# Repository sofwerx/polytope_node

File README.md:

# polytope_node
Compute/Sensor node for Polytope

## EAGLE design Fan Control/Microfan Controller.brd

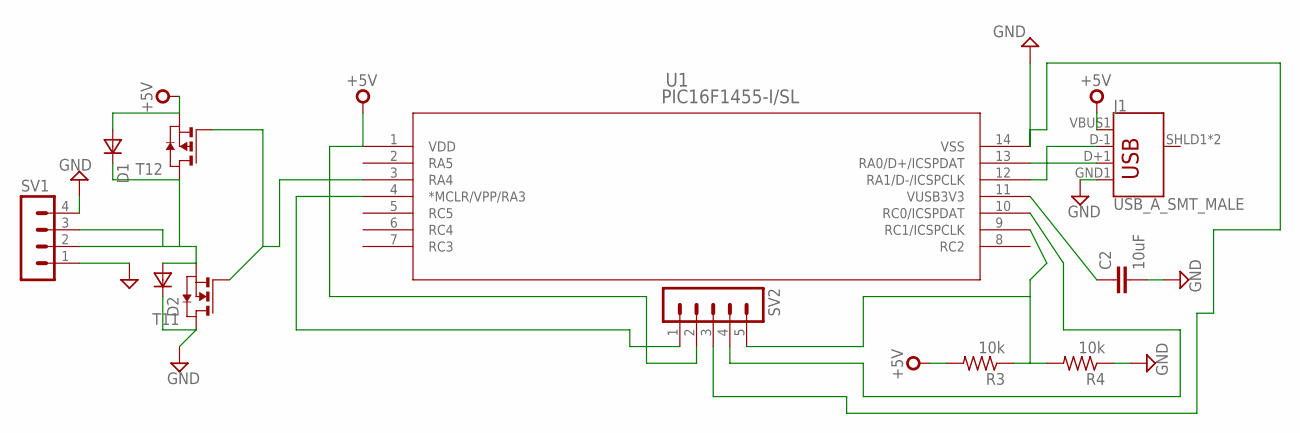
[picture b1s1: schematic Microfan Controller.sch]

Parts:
C2: 10uF; C0805
D1, D2: VAR2SOT23; SOT-23
J1: USB_A_SMT_MALE; USB-A-SMT-MALE
R3, R4: 10k; R0805
SV1: MA04-1
SV2: MA05-1
T1: PN_MOSFET-MSOP8; MSOP8
U1: PIC16F1455-I/SL; SOIC14_SL

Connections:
+5V: D1.3 (A), J1.VBUS1 (VBUS), R3.2, SV2.2, T1.3 (S), U1.1 (VDD)
GND: C2.2, D2.1 (C), J1.GND1 (GND), R4.1, SV1.1, SV1.4, T1.7 (D), T1.8 (D)
unnamed: SV2.1, U1.4 (*MCLR/VPP/RA3)
unnamed: J1.D-1 (D-), U1.12 (RA1/D-/ICSPCLK)
unnamed: T1.2 (G), T1.4 (G), U1.3 (RA4)
unnamed: R3.1, R4.2, SV2.5, U1.9 (RC1/ICSPCLK)
unnamed: D1.1 (C), D2.3 (A), SV1.2, SV1.3, T1.1 (S), T1.5 (D), T1.6 (D)
unnamed: J1.D+1 (D+), U1.13 (RA0/D+/ICSPDAT)
unnamed: SV2.3, U1.14 (VSS)
unnamed: SV2.4, U1.10 (RC0/ICSPDAT)
VUSB3V3: U1.11 (VUSB3V3)

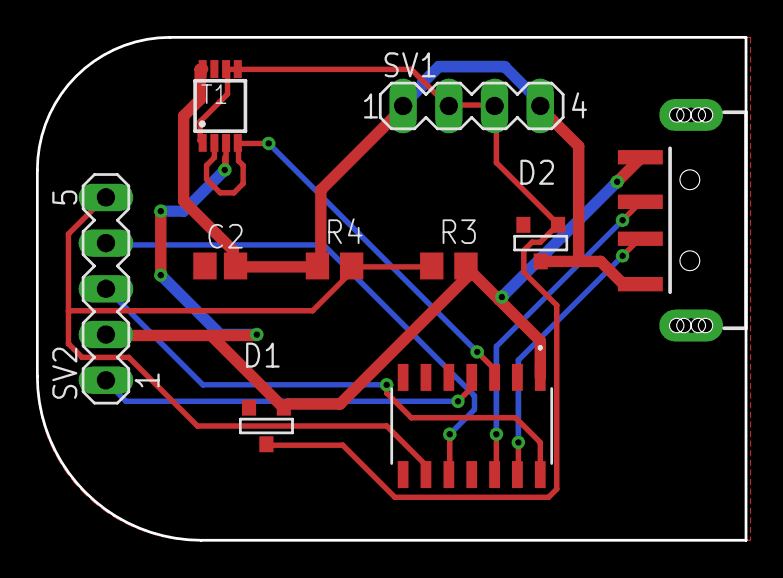
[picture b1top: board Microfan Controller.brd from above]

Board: 2 copper layers, 39.4 x 27.9 mm, 10 parts (0 on the bottom side), 10 nets.

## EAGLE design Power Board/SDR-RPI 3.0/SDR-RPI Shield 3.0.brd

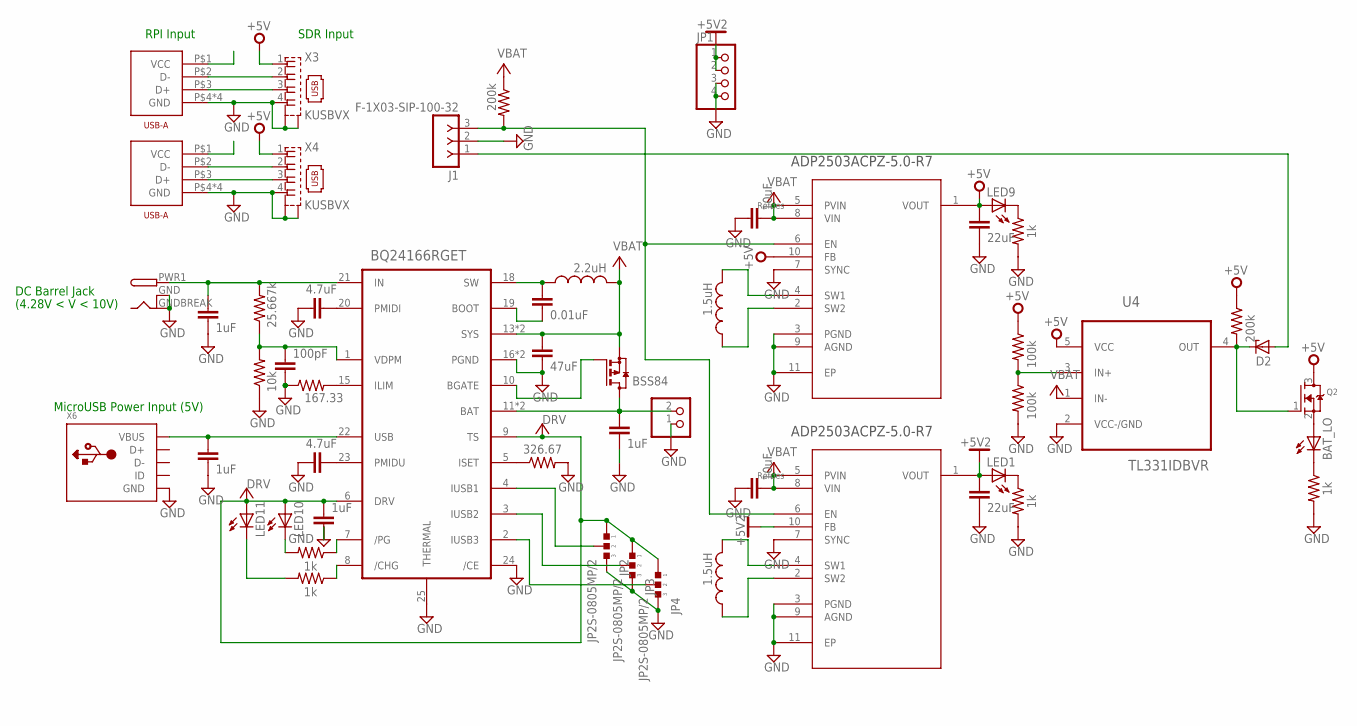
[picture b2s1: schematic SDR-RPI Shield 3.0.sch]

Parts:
BAT_LO: LED_ESML0603; LED_SML0603
C1, C3, C5, C8: 1uF; C0805
C2, C4: 4.7uF; C0805
C6: 0.01uF; C0805
C7, C12: 22uF; C0805
C9: 47uF; C0805
C10, C11: 10uF; C0805
C17: 100pF; C0805
CN1: JST_2PIN-SMT; JST-PH-2-SMT
CN3: DCBARRELSMT; DCJACK_2MM_SMT
D2: ZENER-DIODESOD80C; SOD80C
J1: F-1X03-SIP-100-32; SIP-100-03-32
JP1: PINHD-1X4; 1X04
JP2, JP3, JP4: JP2S-0805MP/2; R0805MP/2
L1: 2.2uH; L1812
L2, L3: 1.5uH; L1812
LED1, LED9, LED10, LED11: LED_ESML0603; LED_SML0603
Q1: BSS84; SOT23
Q2: MOSFET-NREFLOW; SOT23
R1: 25.667k; M0805
R2: 10k; M0805
R3: 167.33; M0805
R4, R5, R7, R8, R12: 1k; M0805
R6: 326.67; M0805
R9, R10: 100k; M0805
R11, R16: 200k; M0805
U1: BQ24166RGET; QFN50P400X400X100-25N
U2, U3: ADP2503ACPZ-5.0-R7; DFN300X300X80-11N
U4: TL331IDBVR; SOT95P280X145-5N
U$1, U$2: USB-A
X3, X4: KUSBVX
X6: USB_MICRO_20329_V2; 4UCONN_20329_V2

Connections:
+5V: C12.1, LED9.A, Q2.3 (D), R9.1, R11.1, U3.1 (VOUT), U3.10 (FB), U4.5 (VCC), X3.1, X4.1
+5V2: C7.1, JP1.1, JP1.2, LED1.A, U2.1 (VOUT), U2.10 (FB)
DRV: C5.1, JP2.1, JP3.1, JP4.1, LED10.A, LED11.A, U1.6 (DRV), U1.9 (TS)
GND: C1.2, C2.2, C3.2, C4.2, C5.2, C7.2, C8.2, C9.2, C10.1, C11.1, C12.2, C17.2, CN1.1 (2), CN3.GND (GNDBREAK), CN3.GNDBREAK (GND), J1.2, JP1.3, JP1.4, JP2.3, JP3.3, JP4.3, R2.1, R3.1, R6.2, R7.2, R8.2, R10.2, R12.2, U1.16 (PGND), U1.17 (PGND), U1.24 (/CE), U1.25 (THERMAL), U2.3 (PGND), U2.7 (SYNC), U2.9 (AGND), U2.11 (EP), U3.3 (PGND), U3.7 (SYNC), U3.9 (AGND), U3.11 (EP), U4.2 (VCC-/GND), U$1.P$4 (GND), U$1.P$5 (GND), U$1.P$6 (GND), U$1.P$8 (GND), U$2.P$4 (GND), U$2.P$5 (GND), U$2.P$6 (GND), U$2.P$8 (GND), X3.4, X3.M1 (S1), X3.M2 (S2), X4.4, X4.M1 (S1), X4.M2 (S2), X6.BASE@1 (GND), X6.BASE@2 (GND), X6.GND, X6.SPRT@1 (GND), X6.SPRT@2 (GND), X6.SPRT@3 (GND), X6.SPRT@4 (GND)
unnamed: C17.1, R1.1, R2.2, U1.1 (VDPM)
unnamed: R4.1, U1.7 (/PG)
unnamed: R5.1, U1.8 (/CHG)
unnamed: C1.1, CN3.PWR1 (PWR), R1.2, U1.21 (IN)
unnamed: C2.1, U1.20 (PMIDI)
unnamed: R3.2, U1.15 (ILIM)
unnamed: C3.1, U1.22 (USB), X6.VBUS
unnamed: C4.1, U1.23 (PMIDU)
unnamed: Q1.1 (G), U1.10 (BGATE)
unnamed: LED10.C, R4.2
unnamed: C6.2, U1.19 (BOOT)
unnamed: LED11.C, R5.2
unnamed: C6.1, L1.1, U1.18 (SW)
unnamed: J1.3, R16.2, U2.6 (EN), U3.6 (EN)
unnamed: L2.2, U3.4 (SW1)
unnamed: L2.1, U3.2 (SW2)
unnamed: C8.1, CN1.2 (1), Q1.3 (D), U1.11 (BAT), U1.12 (BAT)
unnamed: R6.1, U1.5 (ISET)
unnamed: R9.2, R10.1, U4.3 (IN+)
unnamed: LED1.C, R7.1
unnamed: L3.2, U2.4 (SW1)
unnamed: LED9.C, R8.1
unnamed: D2.A, J1.1
unnamed: L3.1, U2.2 (SW2)
unnamed: BAT_LO.A, Q2.2 (S)
unnamed: D2.C, Q2.1 (G), R11.2, U4.4 (OUT)
unnamed: BAT_LO.C, R12.1
unnamed: U$1.P$2 (D-), X3.2
unnamed: U$1.P$3 (D+), X3.3
unnamed: U$2.P$2 (D-), X4.2
unnamed: U$2.P$3 (D+), X4.3
unnamed: JP2.2, U1.4 (IUSB1)
unnamed: JP3.2, U1.3 (IUSB2)
unnamed: JP4.2, U1.2 (IUSB3)
V+: C9.1, C10.2, C11.2, L1.2, Q1.2 (S), R16.1, U1.13 (SYS), U1.14 (SYS), U2.5 (PVIN), U2.8 (VIN), U3.5 (PVIN), U3.8 (VIN), U4.1 (IN-)

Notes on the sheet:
RPI Input
SDR Input
MicroUSB Power Input (5V)
DC Barrel Jack
(4.28V < V < 10V)

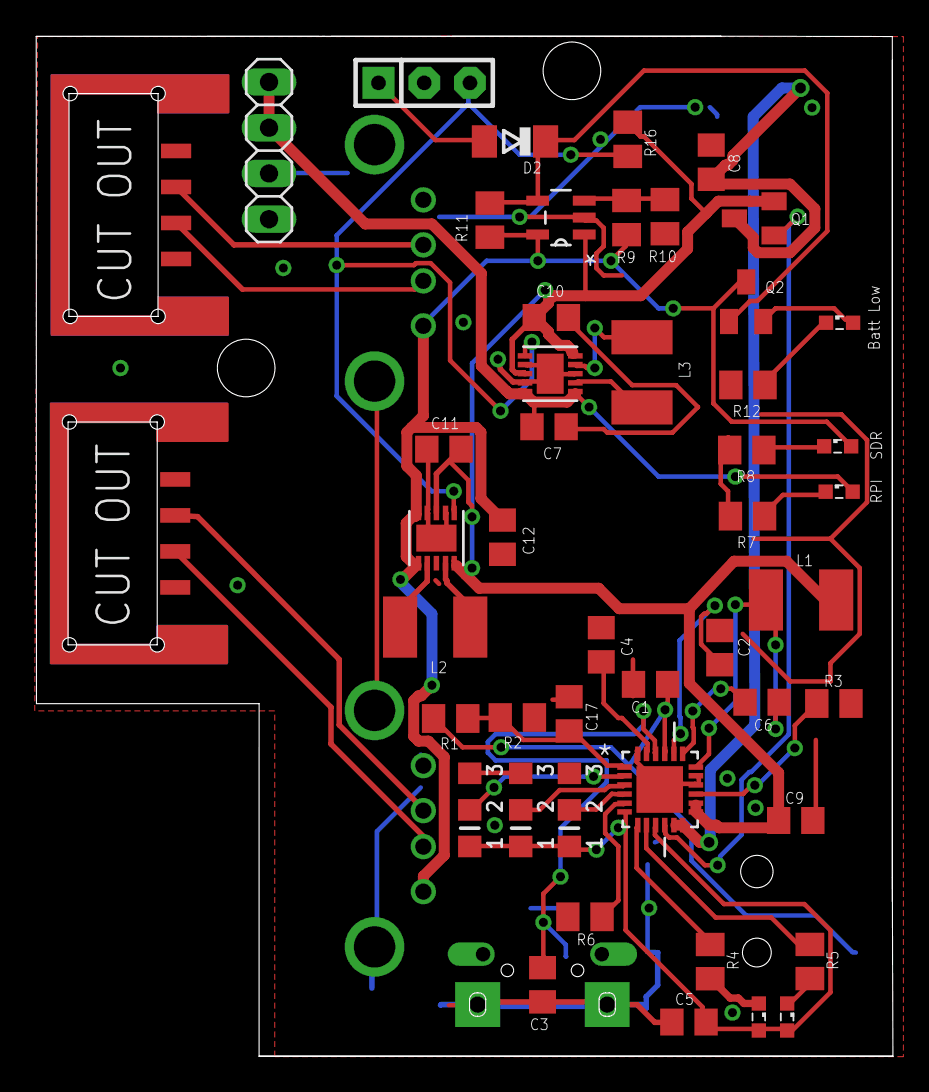
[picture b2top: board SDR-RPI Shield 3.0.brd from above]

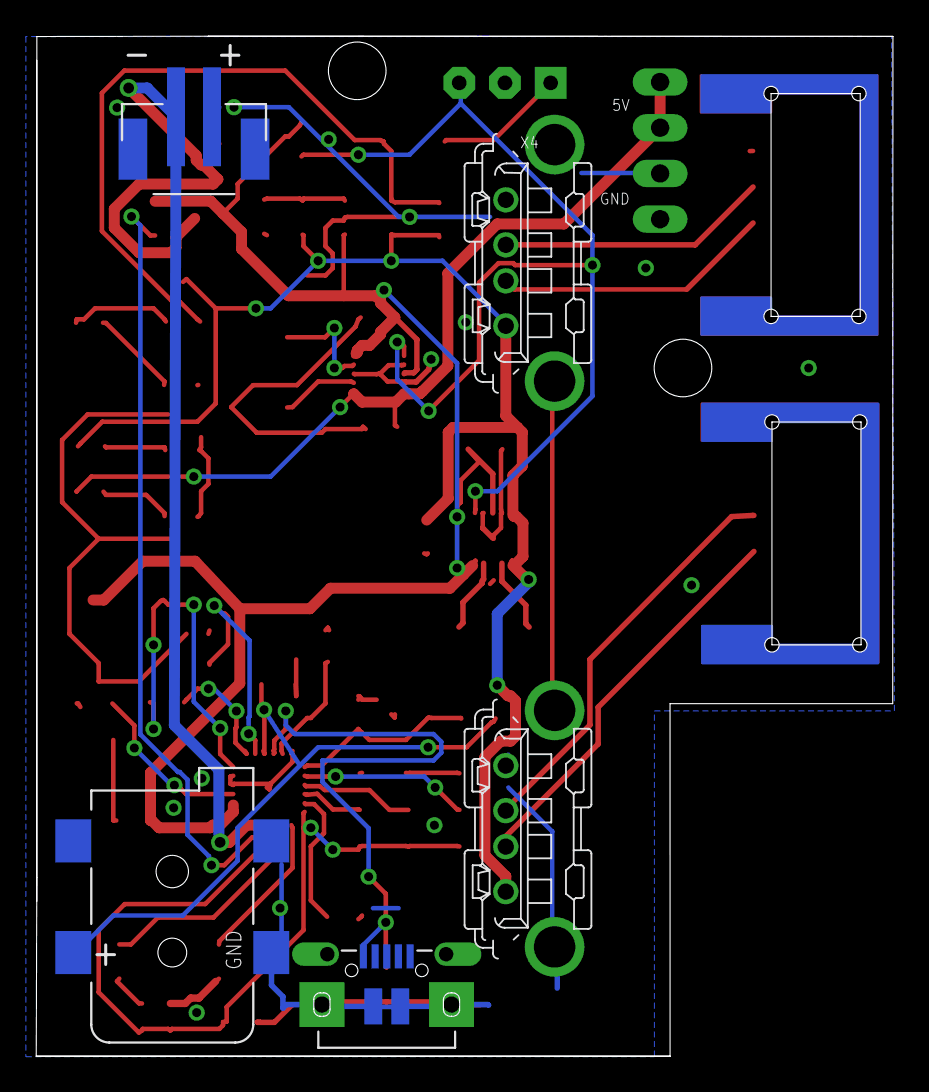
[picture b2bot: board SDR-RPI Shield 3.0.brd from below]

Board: 2 copper layers, 47.6 x 56.7 mm, 53 parts (5 on the bottom side), 39 nets.

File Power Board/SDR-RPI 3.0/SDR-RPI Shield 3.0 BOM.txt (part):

Partlist exported from G:/SOFWERX/SDR-RPI Shield/SDR-RPI Shield 3.0.sch at 4/27/2017 12:59 PM

Qty Value              Device             Package               Parts                            Description                                                     MPN                OC_FARNELL OC_NEWARK PACKAGE  SPICEMODEL SPICEPREFIX SPICETYPE SUPPLIER         
1                      DCBARRELSMT        DCJACK_2MM_SMT        CN3                              2.0mm DC Barrel Jack                                                                                                                                               
1                      JST_2PIN-SMT       JST-PH-2-SMT          CN1                              JST 2-Pin Connectors of various flavors                                                                                                                            
5                      LED_ESML0603       LED_SML0603           BAT_LO, LED1, LED9, LED10, LED11 LED                                                                                                              NONE       D           diode                      
1                      MOSFET-NREFLOW     SOT23                 Q2                               N-Channel Mosfet                                                                                                                                                   
1                      PINHD-1X4          1X04                  JP1                              PIN HEADER                                                                                                                                                         
1                      USB_MICRO_20329_V2 4UCONN_20329_V2       X6                               USB Connectors                                                                                                                                                     
1                      ZENER-DIODESOD80C  SOD80C                D2                               Z-Diode                                                                                                                                                            
1   0.01uF             C-EUC0805          C0805                 C6                               CAPACITOR, European symbol                                                                                                                                         
2   1.5uH              L-USL1812          L1812                 L2, L3                           INDUCTOR, American symbol                                                                                                                                          
2   100k               R-US_M0805         M0805                 R9, R10                          RESISTOR, American symbol                                                                                                                                          
1   100pF              C-EUC0805          C0805                 C17                              CAPACITOR, European symbol                                                                                                                                         
1   10k                R-US_M0805         M0805                 R2                               RESISTOR, American symbol                                                                                                                                          
2   10uF               C-EUC0805          C0805                 C10, C11                         CAPACITOR, European symbol                                                                                                                                         
1   167.33             R-US_M0805         M0805                 R3                               RESISTOR, American symbol                                                                                                                                          
5   1k                 R-US_M0805         M0805                 R4, R5, R7, R8, R12              RESISTOR, American symbol                                                                                                                                          
4   1uF                C-EUC0805          C0805                 C1, C3, C5, C8                   CAPACITOR, European symbol                                                                                                                                         
1   2.2uH              L-USL1812          L1812                 L1                               INDUCTOR, American symbol                                                                                                                                          
2   200k               R-US_M0805         M0805                 R11, R16                         RESISTOR, American symbol                                                                                                                                          
2   22uF               C-EUC0805          C0805                 C7, C12                          CAPACITOR, European symbol                                                                                                                                         
1   25.667k            R-US_M0805         M0805                 R1                               RESISTOR, American symbol                                                                                                                                          
1   326.67             R-US_M0805         M0805                 R6                               RESISTOR, American symbol                                                                                                                                          
2   4.7uF              C-EUC0805          C0805                 C2, C4                           CAPACITOR, European symbol                                                                                                                                         
1   47uF               C-EUC0805          C0805                 C9                               CAPACITOR, European symbol                                                                                                                                         
2   ADP2503ACPZ-5.0-R7 ADP2503ACPZ-5.0-R7 DFN300X300X80-11N     U2, U3                           DC-to-DC Converter                                              ADP2503ACPZ-5.0-R7 -          11R0638   LFCSP-10                                  Analog Devices   
1   BQ24166RGET        BQ24166RGET        QFN50P400X400X100-25N U1                               Li-Polymer Battery Charger                                      BQ24166RGET                             VQFN-24                                   Texas Instruments
1   BSS84              BSS84              SOT23                 Q1                               P-CHANNEL MOS FET                                                                                                                                                  
1   F-1X03-SIP-100-32  F-1X03-SIP-100-32  SIP-100-03-32         J1                               FEMALE HEADER                                                                                                                                                      
3   JP2S-0805MP/2      JP2S-0805MP/2      R0805MP/2             JP2, JP3, JP4                    SMD Jumper/Bridge                                                                                                                                                  
2   KUSBVX             KUSBVX             KUSBVX                X3, X4                           Vertical,Top Entry Universal Serial Bus Connector KUSBVX Series                                                                                                    
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
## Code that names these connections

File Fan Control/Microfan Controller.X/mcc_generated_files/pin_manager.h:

#ifndef PIN_MANAGER_H
#define PIN_MANAGER_H

#define INPUT   1
#define OUTPUT  0

#define HIGH    1
#define LOW     0

#define ANALOG      1
#define DIGITAL     0

#define PULL_UP_ENABLED      1
#define PULL_UP_DISABLED     0

#define IO_RA0_PORT               PORTAbits.RA0
#define IO_RA0_GetValue()           PORTAbits.RA0

#define IO_RA1_PORT               PORTAbits.RA1
#define IO_RA1_GetValue()           PORTAbits.RA1

#define IO_RA4_TRIS               TRISAbits.TRISA4
#define IO_RA4_LAT                LATAbits.LATA4
#define IO_RA4_PORT               PORTAbits.RA4
#define IO_RA4_WPU                WPUAbits.WPUA4
#define IO_RA4_ANS                ANSELAbits.ANSA4
#define IO_RA4_SetHigh()            do { LATAbits.LATA4 = 1; } while(0)
#define IO_RA4_SetLow()             do { LATAbits.LATA4 = 0; } while(0)
#define IO_RA4_Toggle()             do { LATAbits.LATA4 = ~LATAbits.LATA4; } while(0)
#define IO_RA4_GetValue()           PORTAbits.RA4
#define IO_RA4_SetDigitalInput()    do { TRISAbits.TRISA4 = 1; } while(0)
#define IO_RA4_SetDigitalOutput()   do { TRISAbits.TRISA4 = 0; } while(0)
#define IO_RA4_SetPullup()      do { WPUAbits.WPUA4 = 1; } while(0)
#define IO_RA4_ResetPullup()    do { WPUAbits.WPUA4 = 0; } while(0)
#define IO_RA4_SetAnalogMode()  do { ANSELAbits.ANSA4 = 1; } while(0)
#define IO_RA4_SetDigitalMode() do { ANSELAbits.ANSA4 = 0; } while(0)

#define IO_RC0_TRIS               TRISCbits.TRISC0
#define IO_RC0_LAT                LATCbits.LATC0
#define IO_RC0_PORT               PORTCbits.RC0
#define IO_RC0_ANS                ANSELCbits.ANSC0
#define IO_RC0_SetHigh()            do { LATCbits.LATC0 = 1; } while(0)
#define IO_RC0_SetLow()             do { LATCbits.LATC0 = 0; } while(0)
#define IO_RC0_Toggle()             do { LATCbits.LATC0 = ~LATCbits.LATC0; } while(0)
#define IO_RC0_GetValue()           PORTCbits.RC0
#define IO_RC0_SetDigitalInput()    do { TRISCbits.TRISC0 = 1; } while(0)
#define IO_RC0_SetDigitalOutput()   do { TRISCbits.TRISC0 = 0; } while(0)
#define IO_RC0_SetAnalogMode()  do { ANSELCbits.ANSC0 = 1; } while(0)
#define IO_RC0_SetDigitalMode() do { ANSELCbits.ANSC0 = 0; } while(0)

#define IO_RC1_TRIS               TRISCbits.TRISC1
#define IO_RC1_LAT                LATCbits.LATC1
#define IO_RC1_PORT               PORTCbits.RC1
#define IO_RC1_ANS                ANSELCbits.ANSC1
#define IO_RC1_SetHigh()            do { LATCbits.LATC1 = 1; } while(0)
#define IO_RC1_SetLow()             do { LATCbits.LATC1 = 0; } while(0)
#define IO_RC1_Toggle()             do { LATCbits.LATC1 = ~LATCbits.LATC1; } while(0)
#define IO_RC1_GetValue()           PORTCbits.RC1
#define IO_RC1_SetDigitalInput()    do { TRISCbits.TRISC1 = 1; } while(0)
#define IO_RC1_SetDigitalOutput()   do { TRISCbits.TRISC1 = 0; } while(0)
#define IO_RC1_SetAnalogMode()  do { ANSELCbits.ANSC1 = 1; } while(0)
#define IO_RC1_SetDigitalMode() do { ANSELCbits.ANSC1 = 0; } while(0)

void PIN_MANAGER_Initialize (void);
void PIN_MANAGER_IOC(void);



#endif

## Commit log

2017-07-06 Create battery-low.py script
2017-07-06 Create Part Orders
2017-07-06 Create References

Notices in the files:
parts and their libraries:
SparkFun-Connectors: Licensing: Creative Commons ShareAlike 4.0 International - https://creativecommons.org/licenses/by-sa/4.0
COPYRIGHT: Copyright C 2015 Accelerated Designs. All rights reserved
con-headers-jp: Copyright (C) 2008, Bob Starr
jumpers: Copyright (C) 2009, Bob Starr
